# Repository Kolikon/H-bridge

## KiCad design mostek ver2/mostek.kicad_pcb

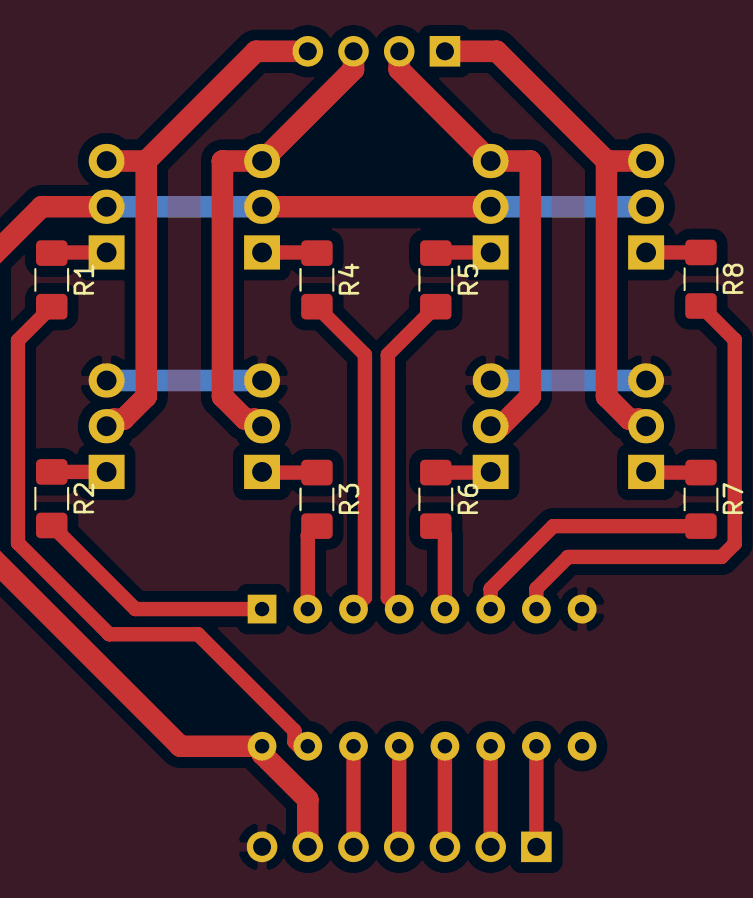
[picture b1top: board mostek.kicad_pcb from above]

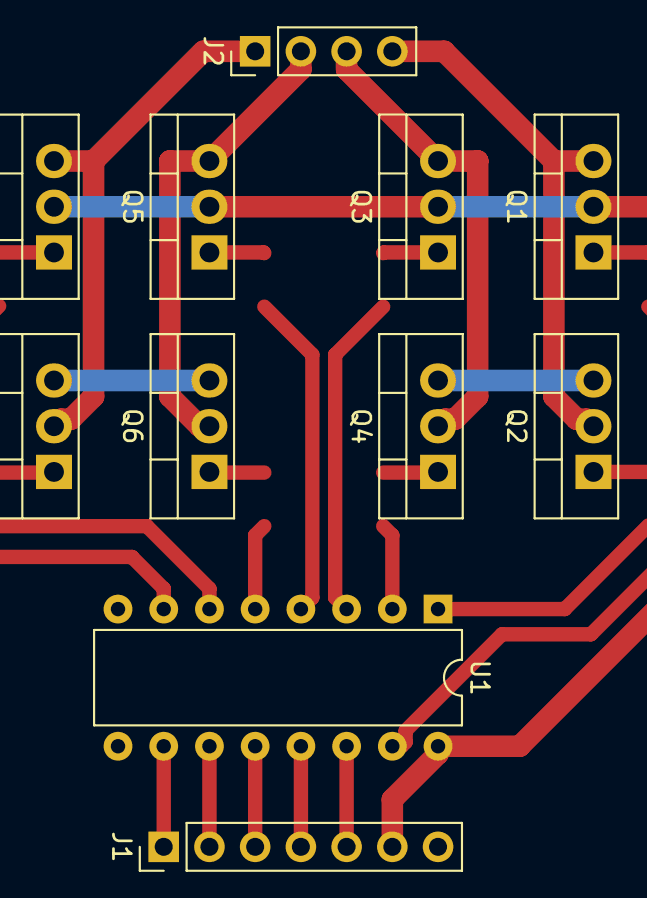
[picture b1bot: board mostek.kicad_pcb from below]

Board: 2 copper layers, 19 parts (11 on the bottom side), 27 nets.

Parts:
J1: Conn_01x07; PinHeader_1x07_P2.54mm_Vertical
J2: Conn_01x04; PinHeader_1x04_P2.54mm_Vertical
Q1, Q2, Q3, Q4, Q5, Q6, Q7, Q8: TIP122; TO-220-3_Vertical
R1, R2, R3, R4, R5, R6, R7, R8: R; R_1206_3216Metric_Pad1.42x1.75mm_HandSolder
U1: 74HC595; DIP-16_W7.62mm

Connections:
GND: J1.7, Q2.3, Q4.3, Q6.3, Q8.3, U1.8
unnamed: J1.1, U1.10
unnamed: J1.2, U1.11
unnamed: J1.3, U1.12
unnamed: J1.4, U1.13
unnamed: J1.5, U1.14
unnamed: J2.1, Q7.3, Q8.2
unnamed: J2.2, Q5.3, Q6.2
unnamed: J2.3, Q3.3, Q4.2
unnamed: J2.4, Q1.3, Q2.2
unnamed: Q1.1, R1.1
unnamed: Q2.1, R2.1
unnamed: Q3.1, R4.1
unnamed: Q4.1, R3.1
unnamed: Q5.1, R5.1
unnamed: Q6.1, R6.1
unnamed: Q7.1, R8.1
unnamed: Q8.1, R7.1
unnamed: R1.2, U1.15
unnamed: R2.2, U1.1
unnamed: R3.2, U1.2
unnamed: R4.2, U1.3
unnamed: R5.2, U1.4
unnamed: R6.2, U1.5
unnamed: R7.2, U1.6
unnamed: R8.2, U1.7
VCC: J1.6, Q1.2, Q3.2, Q5.2, Q7.2, U1.16
